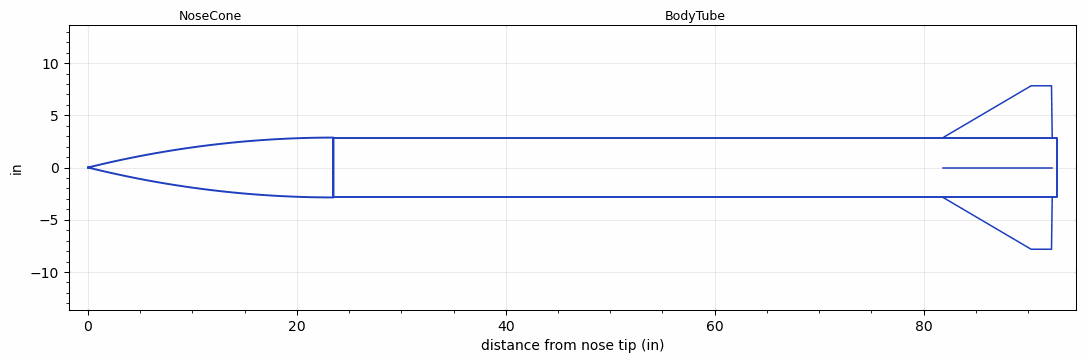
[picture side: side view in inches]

<RASAeroDocument>
 <FileVersion>2</FileVersion>
 <RocketDesign>
  <NoseCone>
   <Length>23.5</Length>
   <Diameter>5.73</Diameter>
   <Shape>Tangent Ogive</Shape>
   <BluntRadius>0.25</BluntRadius>
   <Location>0</Location>
  </NoseCone>
  <BodyTube>
   <Length>69.25</Length>
   <Diameter>5.73</Diameter>
   <LaunchLugDiameter>0.5</LaunchLugDiameter>
   <LaunchLugLength>1</LaunchLugLength>
   <Location>23.5</Location>
   <Fin>
    <Count>4</Count>
    <Chord>10.451</Chord>
    <Span>4.961</Span>
    <SweepDistance>8.432</SweepDistance>
    <TipChord>1.95</TipChord>
    <Thickness>0.5692</Thickness>
    <Location>10.8875</Location>
    <AirfoilSection>Double Wedge</AirfoilSection>
    <FX1>3.1003</FX1>
   </Fin>
  </BodyTube>
  <Surface>Smooth Paint</Surface>
  <ModifiedBarrowman>True</ModifiedBarrowman>
  <Turbulence>False</Turbulence>
  <UseBooster1>False</UseBooster1>
  <UseBooster2>False</UseBooster2>
 </RocketDesign>
 <LaunchSite>
  <Altitude>1214</Altitude>
  <Pressure>30.18</Pressure>
  <RodAngle>6</RodAngle>
  <RodLength>15</RodLength>
  <Temperature>59</Temperature>
  <WindSpeed>9.32</WindSpeed>
 </LaunchSite>
 <Recovery>
  <Altitude1>656.168</Altitude1>
  <Altitude2>1500</Altitude2>
  <DeviceType1>Parachute</DeviceType1>
  <DeviceType2>Parachute</DeviceType2>
  <Event1>True</Event1>
  <Event2>True</Event2>
  <Size1>28.01</Size1>
  <Size2>72</Size2>
  <EventType1>Apogee</EventType1>
  <EventType2>Altitude</EventType2>
  <CD1>1.5</CD1>
  <CD2>2.2</CD2>
 </Recovery>
 <SimulationList>
  <Simulation>
   <SustainerEngine>N2540-GR-P  (CTI)</SustainerEngine>
   <SustainerLaunchWt>58.64</SustainerLaunchWt>
   <SustainerNozzleDiameter>2.37</SustainerNozzleDiameter>
   <SustainerCG>60.31</SustainerCG>
   <SustainerIgnitionDelay>0</SustainerIgnitionDelay>
   <Booster1SeparationDelay>0</Booster1SeparationDelay>
   <Booster1IgnitionDelay>0</Booster1IgnitionDelay>
   <IncludeBooster1>False</IncludeBooster1>
   <Booster2Delay>0</Booster2Delay>
   <IncludeBooster2>False</IncludeBooster2>
   <TimetoApogee>35.2001</TimetoApogee>
   <MaxAltitude>24059.2</MaxAltitude>
   <MaxVelocity>1913.955</MaxVelocity>
  </Simulation>
  <Simulation>
   <SustainerLaunchWt>65.9603</SustainerLaunchWt>
   <SustainerCG>65.3991</SustainerCG>
   <SustainerIgnitionDelay>0</SustainerIgnitionDelay>
   <Booster1SeparationDelay>0</Booster1SeparationDelay>
   <Booster1IgnitionDelay>0</Booster1IgnitionDelay>
   <IncludeBooster1>False</IncludeBooster1>
   <Booster2Delay>0</Booster2Delay>
   <IncludeBooster2>False</IncludeBooster2>
  </Simulation>
  <Simulation>
   <SustainerLaunchWt>64.7224</SustainerLaunchWt>
   <SustainerCG>65.2686</SustainerCG>
   <SustainerIgnitionDelay>0</SustainerIgnitionDelay>
   <Booster1SeparationDelay>0</Booster1SeparationDelay>
   <Booster1IgnitionDelay>0</Booster1IgnitionDelay>
   <IncludeBooster1>False</IncludeBooster1>
   <Booster2Delay>0</Booster2Delay>
   <IncludeBooster2>False</IncludeBooster2>
  </Simulation>
  <Simulation>
   <SustainerLaunchWt>55.8785</SustainerLaunchWt>
   <SustainerCG>66.1409</SustainerCG>
   <SustainerIgnitionDelay>0</SustainerIgnitionDelay>
   <Booster1SeparationDelay>0</Booster1SeparationDelay>
   <Booster1IgnitionDelay>0</Booster1IgnitionDelay>
   <IncludeBooster1>False</IncludeBooster1>
   <Booster2Delay>0</Booster2Delay>
   <IncludeBooster2>False</IncludeBooster2>
  </Simulation>
 </SimulationList>
</RASAeroDocument>
